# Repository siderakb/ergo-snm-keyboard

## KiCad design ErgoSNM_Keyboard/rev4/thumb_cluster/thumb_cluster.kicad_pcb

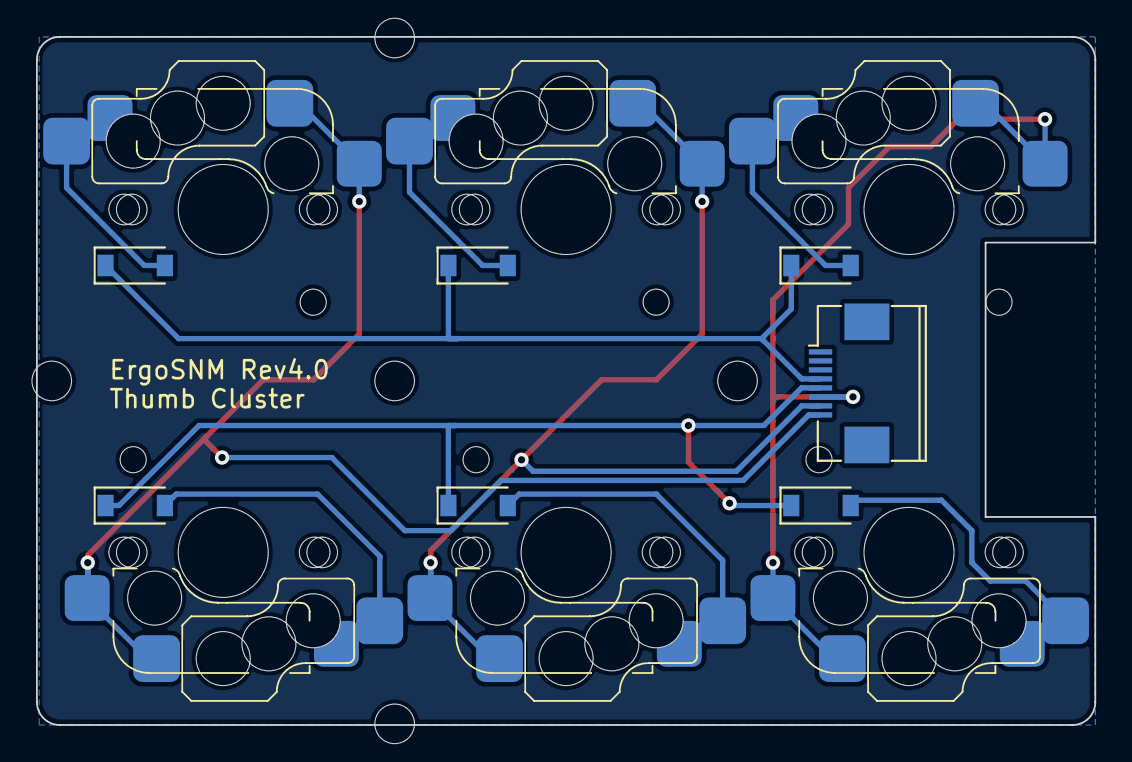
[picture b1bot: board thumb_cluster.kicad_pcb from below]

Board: 2 copper layers, 58.8 x 38.2 mm, 18 parts (11 on the bottom side), 11 nets.

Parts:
D1, D2, D3, D4, D5, D6: 1N4148; D_SOD-123
H1, H2, H3, H4, H5: MountingHole; MountingHole_2.2mm_M2
J2: Conn_FPC; FPC_8P_0.5mm_AFC01-S08FCA-00
KEY1, KEY2, KEY3, KEY4, KEY5, KEY6: SW_Push_45deg; SW_MX_Kailh_Choc_V1V2_HotSwap_Hybrid_alt1

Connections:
COL_5: J2.6, KEY1.1, KEY4.1
COL_6: J2.7, KEY2.1, KEY5.1
COL_7: J2.8, KEY3.1, KEY6.1
unnamed: D1.2 (A), KEY1.2
unnamed: D2.2 (A), KEY2.2
unnamed: D3.2 (A), KEY3.2
unnamed: D4.2 (A), KEY4.2
unnamed: D5.2 (A), KEY5.2
unnamed: D6.2 (A), KEY6.2
ROW_4: D1.1 (K), D2.1 (K), D3.1 (K), J2.4
ROW_5: D4.1 (K), D5.1 (K), D6.1 (K), J2.5

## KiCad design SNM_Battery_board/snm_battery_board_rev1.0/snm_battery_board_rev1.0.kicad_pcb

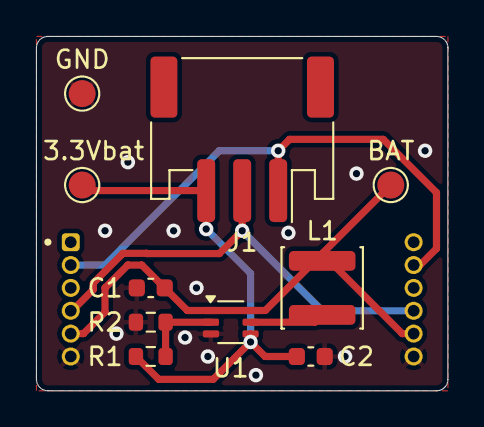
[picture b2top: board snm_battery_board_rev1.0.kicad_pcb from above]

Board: 2 copper layers, 22.9 x 19.7 mm, 11 parts (0 on the bottom side), 7 nets.

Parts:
C1, C2: 10uF; C_0603_1608Metric
J1: Ext. SW_SPDT; JST_PH_S3B-PH-SM4-TB_1x03-1MP_P2.00mm_Horizontal
L1: 4.7uH; L_Changjiang_FNR4030S
M1: SNM_Battery_board
R1: 1.2M; R_0603_1608Metric
R2: 220k; R_0603_1608Metric
TP1: BAT; TestPoint_Pad_D1.5mm
TP2: 3.3Vbat; TestPoint_Pad_D1.5mm
TP3: GND; TestPoint_Pad_D1.5mm
U1: TPS61220DCK; Texas_R-PDSO-G6

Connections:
3.3Vin: J1.1, M1.2, M1.8
3.3Vout: J1.2, M1.4, M1.10
/Vbat: C2.1, J1.3, R1.1, TP2.1, U1.4 (VOUT)
GND: C1.2, C2.2, M1.6, M1.12, R2.2, TP3.1, U1.3 (GND)
unnamed: R1.2, R2.1, U1.2 (FB)
unnamed: L1.2, U1.5 (L)
VBAT: C1.1, L1.1, M1.5, M1.11, TP1.1, U1.1 (VIN), U1.6 (EN)

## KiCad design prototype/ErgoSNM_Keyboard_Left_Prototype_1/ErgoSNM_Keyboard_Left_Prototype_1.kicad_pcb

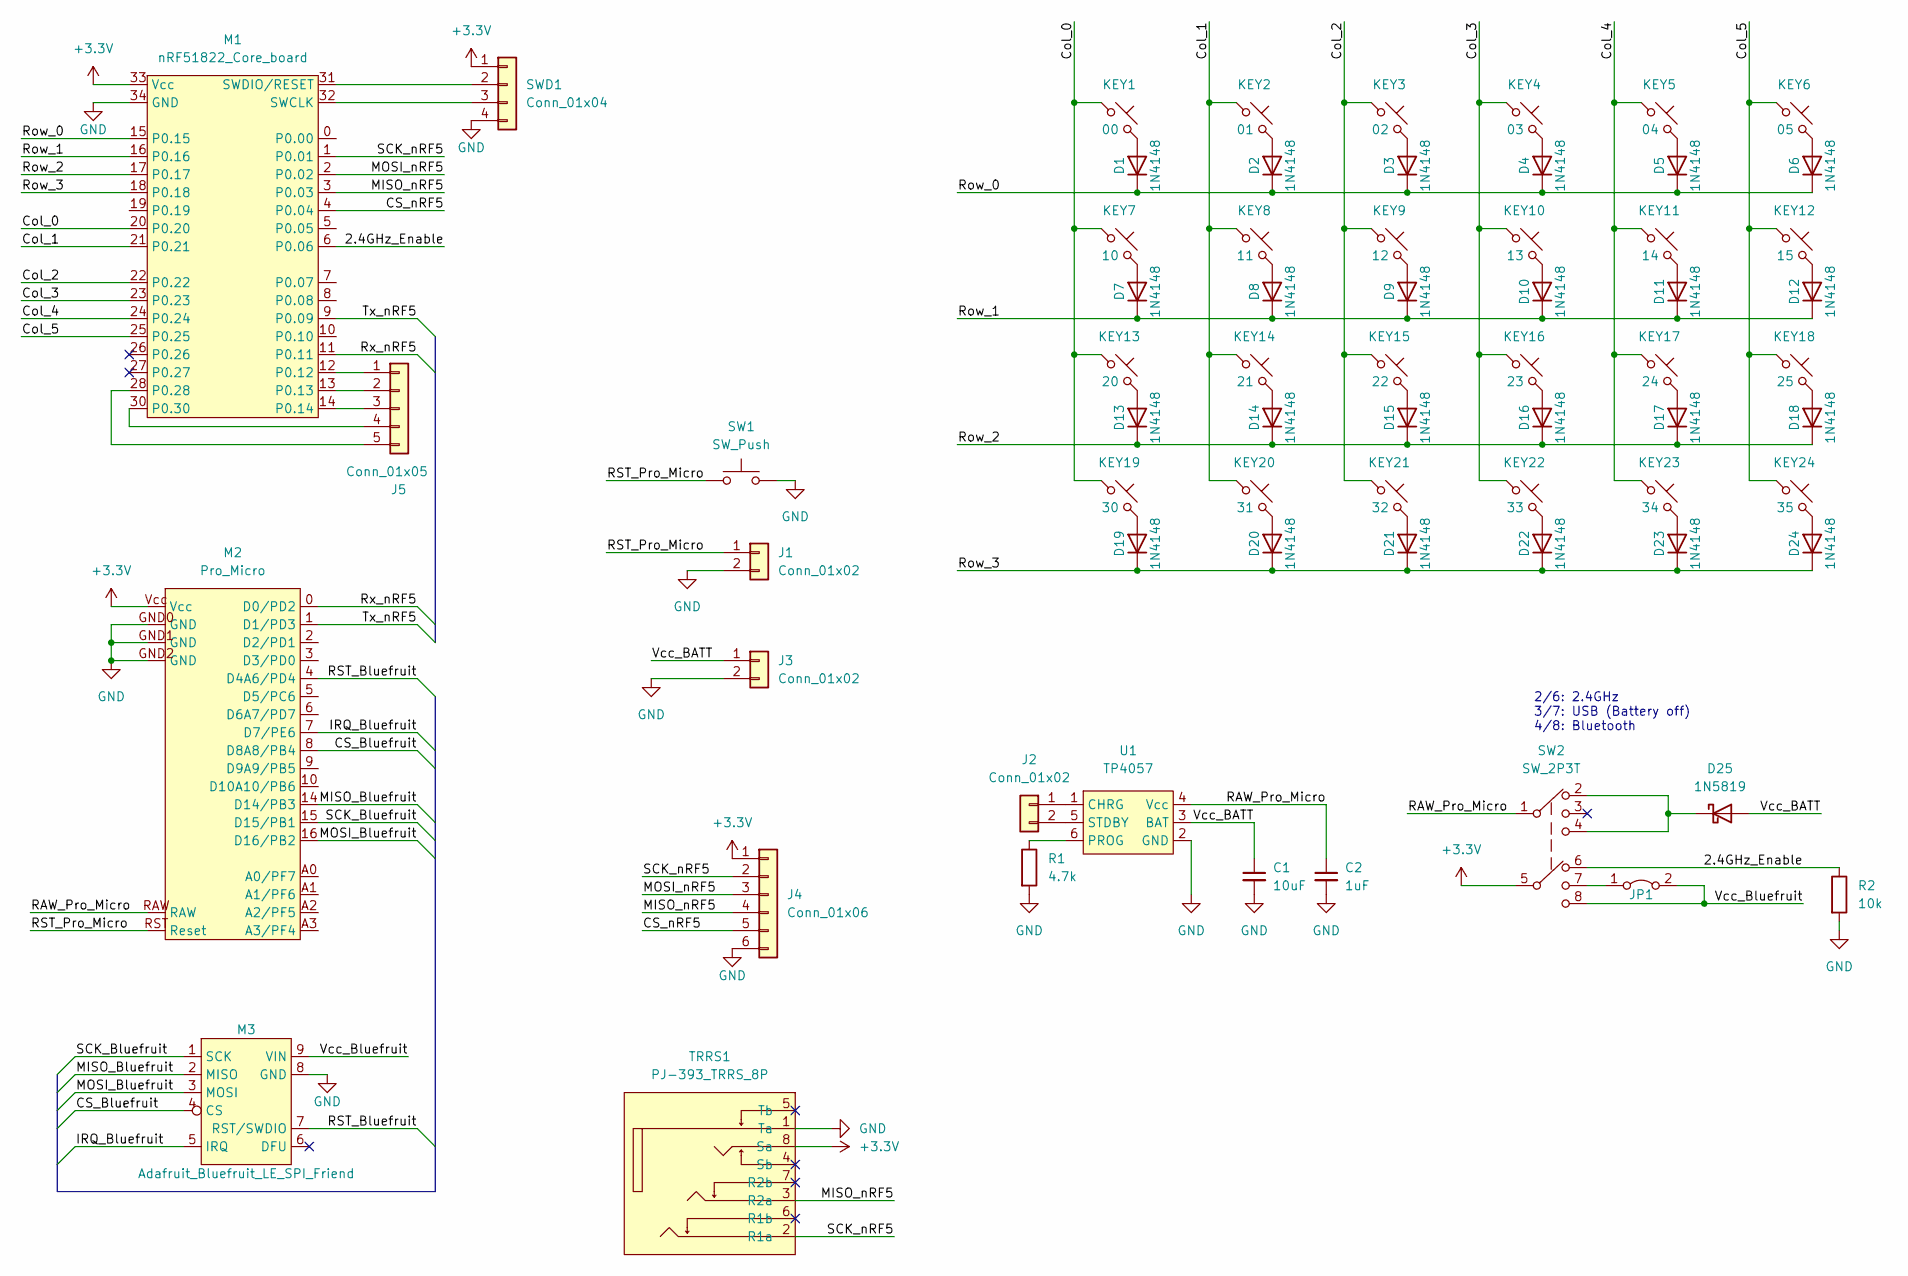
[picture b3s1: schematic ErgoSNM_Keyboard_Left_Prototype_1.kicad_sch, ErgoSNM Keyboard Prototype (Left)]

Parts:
C1: 10uF; C_0201_0603Metric_Pad0.64x0.40mm_HandSolder
C2: 1uF; C_0201_0603Metric_Pad0.64x0.40mm_HandSolder
D1, D2, D3, D4, D5, D6, D7, D8, D9, D10, D11, D12, D13, D14, D15, D16, D17, D18, D19, D20, D21, D22, D23, D24: 1N4148; D_0603_1608Metric_Pad1.05x0.95mm_HandSolder
D25: 1N5819; D_DO-41_SOD81_P10.16mm_Horizontal
J1, J2: Conn_01x02; PinHeader_1x02_P2.54mm_Horizontal
J3: Conn_01x02; JST_EH_B2B-EH-A_1x02_P2.50mm_Vertical
J4: Conn_01x06; PinHeader_1x06_P2.54mm_Vertical
J5: Conn_01x05; PinHeader_1x05_P2.54mm_Vertical
JP1: Jumper_2_Bridged; SolderJumper-2_P1.3mm_Open_TrianglePad1.0x1.5mm
KEY1: 00; MX_Switch_Gateron_socket_A
KEY2: 01; MX_Switch_Gateron_socket_A
KEY3: 02; MX_Switch_Gateron_socket_A
KEY4: 03; MX_Switch_Gateron_socket_A
KEY5: 04; MX_Switch_Gateron_socket_A
KEY6: 05; MX_Switch_Gateron_socket_A
KEY7: 10; MX_Switch_Gateron_socket_A
KEY8: 11; MX_Switch_Gateron_socket_A
KEY9: 12; MX_Switch_Gateron_socket_A
KEY10: 13; MX_Switch_Gateron_socket_A
KEY11: 14; MX_Switch_Gateron_socket_A
KEY12: 15; MX_Switch_Gateron_socket_A
KEY13: 20; MX_Switch_Gateron_socket_A
KEY14: 21; MX_Switch_Gateron_socket_A
KEY15: 22; MX_Switch_Gateron_socket_A
KEY16: 23; MX_Switch_Gateron_socket_A
KEY17: 24; MX_Switch_Gateron_socket_A
KEY18: 25; MX_Switch_Gateron_socket_A
KEY19: 30; MX_Switch_Gateron_socket_A
KEY20: 31; MX_Switch_Gateron_socket_A
KEY21: 32; MX_Switch_Gateron_socket_A
KEY22: 33; MX_Switch_Gateron_socket_A
KEY23: 34; MX_Switch_Gateron_socket_A
KEY24: 35; MX_Switch_Gateron_socket_A
M1: nRF51822_Core_board; Core51822
M2: Pro_Micro
M3: Adafruit_Bluefruit_LE_SPI_Friend; PinHeader_1x09_P2.54mm_Vertical
R1: 4.7k; R_0201_0603Metric_Pad0.64x0.40mm_HandSolder
R2: 10k; R_0201_0603Metric_Pad0.64x0.40mm_HandSolder
SW1: SW_Push; SW_Push_1P1T_NO_CK_KSC6xxJ
SW2: SW_2P3T; MSK-23D20-T
SWD1: Conn_01x04; PinHeader_1x04_P2.54mm_Horizontal
TRRS1: PJ-393_TRRS_8P; PJ-393
U1: TP4057; SOT-23-6_Handsoldering

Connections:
+3V3: J4.1, M1.33 (Vcc), M2.Vcc, SW2.5, SWD1.1, TRRS1.8 (Sa)
/2.4GHz_Enable: M1.6 (P0.06), R2.1, SW2.6
/CS_Bluefruit: M2.8 (D8A8/PB4), M3.4 (CS)
/CS_nRF5: J4.5, M1.4 (P0.04)
/Col_0: KEY1.1, KEY7.1, KEY13.1, KEY19.1, M1.20 (P0.20)
/Col_1: KEY2.1, KEY8.1, KEY14.1, KEY20.1, M1.21 (P0.21)
/Col_2: KEY3.1, KEY9.1, KEY15.1, KEY21.1, M1.22 (P0.22)
/Col_3: KEY4.1, KEY10.1, KEY16.1, KEY22.1, M1.23 (P0.23)
/Col_4: KEY5.1, KEY11.1, KEY17.1, KEY23.1, M1.24 (P0.24)
/Col_5: KEY6.1, KEY12.1, KEY18.1, KEY24.1, M1.25 (P0.25)
/IRQ_Bluefruit: M2.7 (D7/PE6), M3.5 (IRQ)
/MISO_Bluefruit: M2.14 (D14/PB3), M3.2 (MISO)
/MISO_nRF5: J4.4, M1.3 (P0.03), TRRS1.3 (R2a)
/MOSI_Bluefruit: M2.16 (D16/PB2), M3.3 (MOSI)
/MOSI_nRF5: J4.3, M1.2 (P0.02)
/RAW_Pro_Micro: C2.1, M2.RAW, SW2.1, U1.4 (Vcc)
/RST_Bluefruit: M2.4 (D4A6/PD4), M3.7 (RST/SWDIO)
/RST_Pro_Micro: J1.1, M2.RST (Reset), SW1.2
/Row_0: D1.1 (K), D2.1 (K), D3.1 (K), D4.1 (K), D5.1 (K), D6.1 (K), M1.15 (P0.15)
/Row_1: D7.1 (K), D8.1 (K), D9.1 (K), D10.1 (K), D11.1 (K), D12.1 (K), M1.16 (P0.16)
/Row_2: D13.1 (K), D14.1 (K), D15.1 (K), D16.1 (K), D17.1 (K), D18.1 (K), M1.17 (P0.17)
/Row_3: D19.1 (K), D20.1 (K), D21.1 (K), D22.1 (K), D23.1 (K), D24.1 (K), M1.18 (P0.18)
/Rx_nRF5: M1.11 (P0.11), M2.0 (D0/PD2)
/SCK_Bluefruit: M2.15 (D15/PB1), M3.1 (SCK)
/SCK_nRF5: J4.2, M1.1 (P0.01), TRRS1.2 (R1a)
/Tx_nRF5: M1.9 (P0.09), M2.1 (D1/PD3)
/Vcc_BATT: C1.1, D25.2 (A), J3.1, U1.3 (BAT)
/Vcc_Bluefruit: JP1.2 (B), M3.9 (VIN), SW2.8
GND: C1.2, C2.2, J1.2, J3.2, J4.6, M1.34 (GND), M2.GND0 (GND), M2.GND1 (GND), M2.GND2 (GND), M3.8 (GND), R1.2, R2.2, SW1.1, SWD1.4, TRRS1.1 (Ta), U1.2 (GND)
unnamed: D1.2 (A), KEY1.2
unnamed: D2.2 (A), KEY2.2
unnamed: D3.2 (A), KEY3.2
unnamed: D4.2 (A), KEY4.2
unnamed: D5.2 (A), KEY5.2
unnamed: D6.2 (A), KEY6.2
unnamed: D7.2 (A), KEY7.2
unnamed: D8.2 (A), KEY8.2
unnamed: D9.2 (A), KEY9.2
unnamed: D10.2 (A), KEY10.2
unnamed: D11.2 (A), KEY11.2
unnamed: D12.2 (A), KEY12.2
unnamed: D13.2 (A), KEY13.2
unnamed: D14.2 (A), KEY14.2
unnamed: D15.2 (A), KEY15.2
unnamed: D16.2 (A), KEY16.2
unnamed: D17.2 (A), KEY17.2
unnamed: D18.2 (A), KEY18.2
unnamed: D19.2 (A), KEY19.2
unnamed: D20.2 (A), KEY20.2
unnamed: D21.2 (A), KEY21.2
unnamed: D22.2 (A), KEY22.2
unnamed: D23.2 (A), KEY23.2
unnamed: D24.2 (A), KEY24.2
unnamed: D25.1 (K), SW2.2, SW2.4
unnamed: J2.1, U1.1 (CHRG)
unnamed: J2.2, U1.5 (STDBY)
unnamed: JP1.1 (A), SW2.7
unnamed: J5.1, M1.12 (P0.12)
unnamed: J5.2, M1.13 (P0.13)
unnamed: J5.3, M1.14 (P0.14)
unnamed: J5.5, M1.28 (P0.28)
unnamed: J5.4, M1.30 (P0.30)
unnamed: M1.31 (SWDIO/RESET), SWD1.2
unnamed: M1.32 (SWCLK), SWD1.3
unnamed: R1.1, U1.6 (PROG)

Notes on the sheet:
2/6: 2.4GHz 3/7: USB (Battery off) 4/8: Bluetooth

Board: 2 copper layers, 67 parts (0 on the bottom side), 65 nets, no tracks yet.

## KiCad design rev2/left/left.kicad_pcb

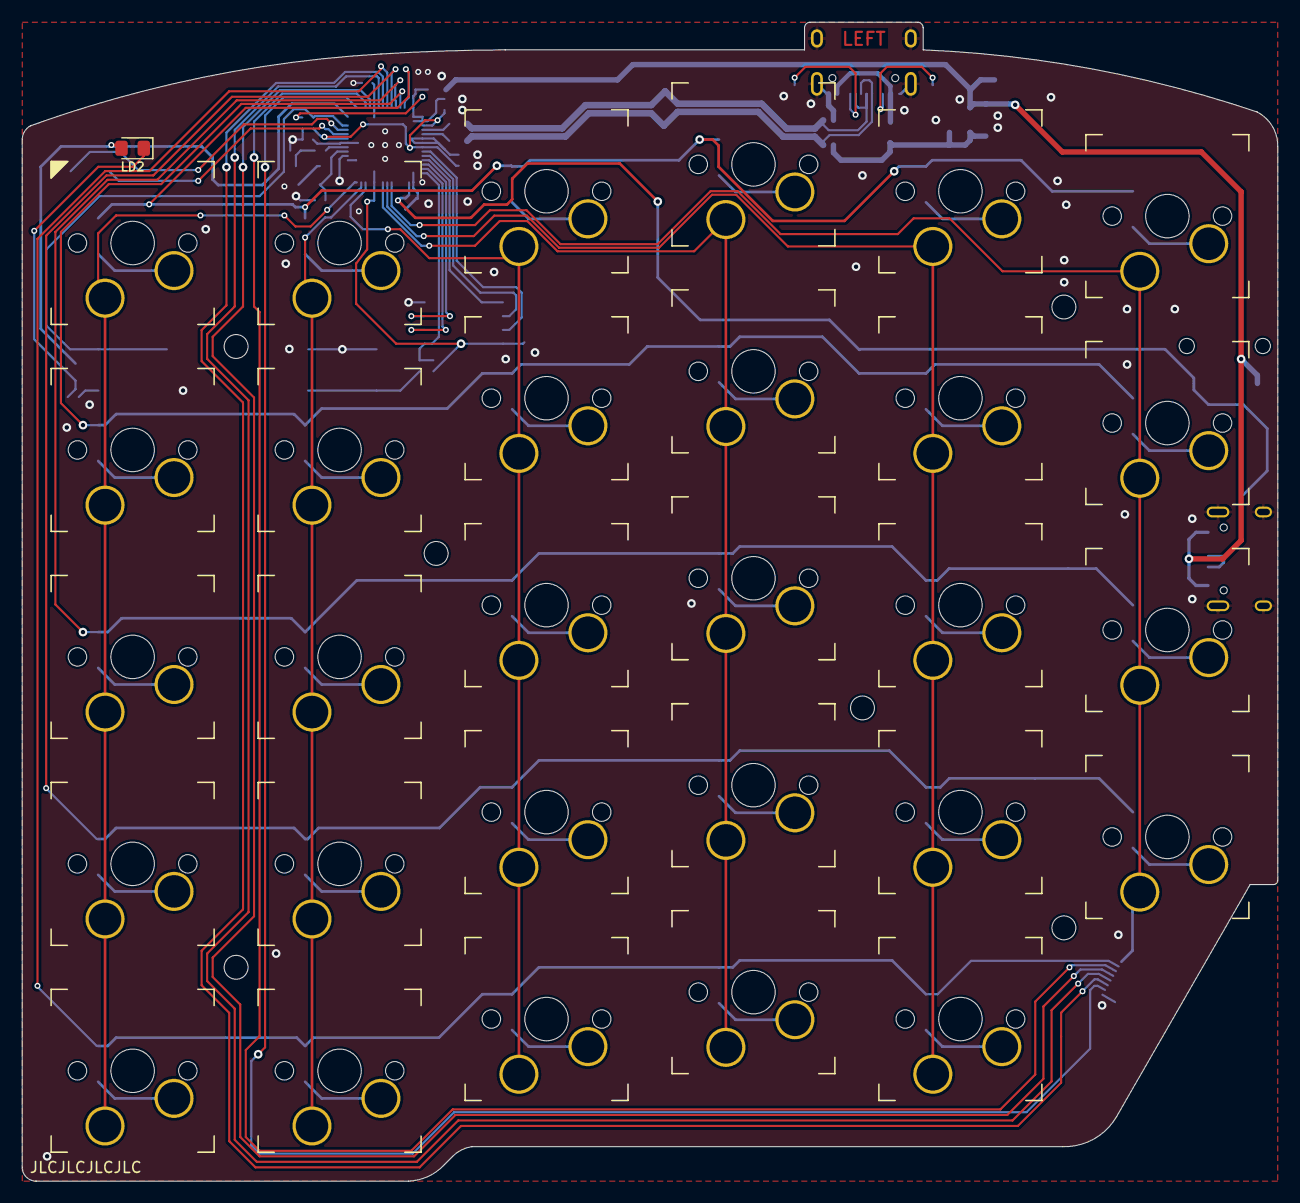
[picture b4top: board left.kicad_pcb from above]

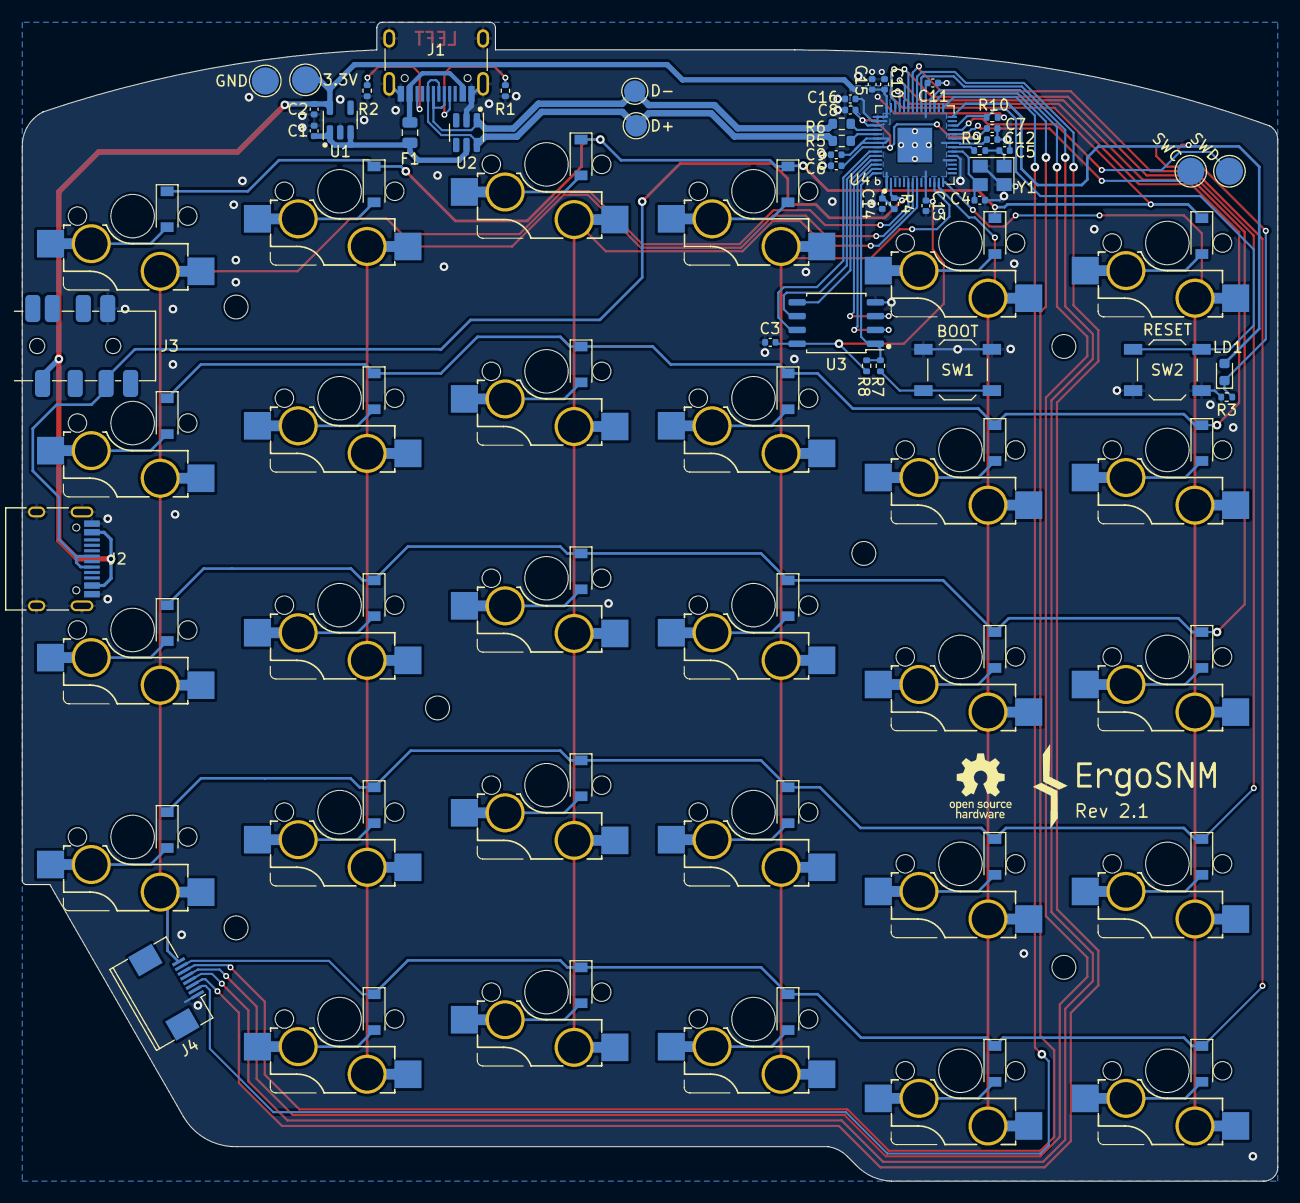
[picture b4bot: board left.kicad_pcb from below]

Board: 2 copper layers, 115.6 x 106.7 mm, 110 parts (80 on the bottom side), 72 nets.

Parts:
C1, C2, C8, C16: 1uF; C_0402_1005Metric
C3, C6, C7, C9, C10, C11, C12, C13, C14, C15: 100nF; C_0402_1005Metric
C4, C5: 20pF; C_0402_1005Metric
D1, D2, D3, D4, D5, D6, D7, D8, D9, D10, D11, D12, D13, D14, D15, D16, D17, D18, D19, D20, D21, D22, D23, D24, D25, D26, D27, D28, D29: 1N4148; D_SOD-123
F1: 500mA, 6V; Fuse_0805_2012Metric
H1, H2, H3, H4, H5, H6: MountingHole; MountingHole_2.2mm_M2
J1, J2: USB_C_Receptacle_USB2.0; USB_C_Receptacle_HRO_TYPE-C-31-M-12
J3: PJ-393_TRRS_8P; PJ-393 8P TRRS
J4: Conn_01x08; FPC_8P_0.5mm_AFC01-S08FCA-00
KEY1, KEY2, KEY3, KEY4, KEY5, KEY6, KEY7, KEY8, KEY9, KEY10, KEY11, KEY12, KEY13, KEY14, KEY15, KEY16, KEY17, KEY18, KEY19, KEY20, KEY21, KEY22, KEY23, KEY24, KEY25, KEY26, KEY27, KEY28, KEY29: SW_Push_45deg; MX_switch_PTH_hotswap_A
LD1: Red; LED_0603_1608Metric
LD2: LED; LED_0805_2012Metric_Pad1.15x1.40mm_HandSolder
R1, R2, R4: 5.1k; R_0402_1005Metric
R3, R7, R9: 1k; R_0402_1005Metric
R5, R6: 27; R_0603_1608Metric
R8, R10: 10k; R_0402_1005Metric
SW1: BOOT; SW_SPST_TL3342
SW2: RESET; SW_SPST_TL3342
TP1, TP4, TP5, TP6: TestPoint; TestPoint_Pad_D2.5mm
TP2, TP3: TestPoint; TestPoint_Pad_D2.0mm
U1: RT9013-33GB; SOT-23-5
U2: SRV05-4; SOT-23-6
U3: W25Q128JVS; SOIC-8_5.23x5.23mm_P1.27mm
U4: RP2040; QFN-56-1EP_7x7mm_P0.4mm_EP3.2x3.2mm
Y1: 12MHz; Crystal_SMD_3225-4Pin_3.2x2.5mm

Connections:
+1V1: C6.1, C7.1, C8.1, U4.23 (DVDD), U4.45 (VREG_VOUT), U4.50 (DVDD)
+3V3: C2.1, C3.1, C9.1, C10.1, C11.1, C12.1, C13.1, C14.1, C15.1, C16.1, J2.A4 (VBUS), J2.A9 (VBUS), J2.B4 (VBUS), J2.B9 (VBUS), J3.S, R4.2, R8.1, R10.1, TP1.1, U1.5 (VOUT), U3.8 (VCC), U4.1 (IOVDD), U4.10 (IOVDD), U4.18 (GPIO15), U4.22 (IOVDD), U4.33 (IOVDD), U4.42 (IOVDD), U4.43 (ADC_AVDD), U4.44 (VREG_IN), U4.48 (USB_VDD), U4.49 (IOVDD)
+5V: C1.1, F1.2, U1.1 (VIN), U1.3 (EN), U2.5 (VP)
/RP2040/BOOT: R7.1, SW1.2
/RP2040/QSPI_D0: U3.5 (DI(IO0)), U4.53 (QSPI_SD0)
/RP2040/QSPI_D1: U3.2 (DO(IO1)), U4.55 (QSPI_SD1)
/RP2040/QSPI_D2: U3.3 (IO2), U4.54 (QSPI_SD2)
/RP2040/QSPI_D3: U3.7 (IO3), U4.51 (QSPI_SD3)
/RP2040/QSPI_SCLK: U3.6 (CLK), U4.52 (QSPI_SCLK)
/RP2040/QSPI_SS: R7.2, R8.2, U3.1 (~CS), U4.56 (QSPI_SS)
/RP2040/SWCLK: TP5.1, U4.24 (SWCLK)
/RP2040/SWDIO: TP6.1, U4.25 (SWD)
/RP2040/~RESET: R10.2, SW2.2, U4.26 (RUN)
/USB_D+: J1.A6 (D+), J1.B6 (D+), R5.1, TP3.1, U2.6 (IO4)
/USB_D-: J1.A7 (D-), J1.B7 (D-), R6.1, TP2.1, U2.1 (IO1)
COL_0: KEY1.1, KEY7.1, KEY13.1, KEY19.1, KEY25.1, U4.14 (GPIO11)
COL_1: KEY2.1, KEY8.1, KEY14.1, KEY20.1, KEY26.1, U4.13 (GPIO10)
COL_2: KEY3.1, KEY9.1, KEY15.1, KEY21.1, KEY27.1, U4.12 (GPIO9)
COL_3: KEY4.1, KEY10.1, KEY16.1, KEY22.1, KEY28.1, U4.8 (GPIO6)
COL_4: KEY5.1, KEY11.1, KEY17.1, KEY23.1, KEY29.1, U4.7 (GPIO5)
COL_5: J4.8, KEY6.1, KEY12.1, KEY18.1, KEY24.1, U4.6 (GPIO4)
COL_6: J4.4, U4.34 (GPIO22)
COL_7: J4.5, U4.32 (GPIO21)
Encoder_A: J4.3, U4.35 (GPIO23)
Encoder_B: J4.2, U4.29 (GPIO18)
GND: C1.2, C2.2, C3.2, C4.1, C5.1, C6.2, C7.2, C8.2, C9.2, C10.2, C11.2, C12.2, C13.2, C14.2, C15.2, C16.2, J1.A1 (GND), J1.A12 (GND), J1.B1 (GND), J1.B12 (GND), J1.S1 (SHIELD), J2.A1 (GND), J2.A12 (GND), J2.B1 (GND), J2.B12 (GND), J2.S1 (SHIELD), J3.T, J4.1, R1.2, R2.2, R3.2, SW1.1, SW2.1, TP4.1, U1.2 (GND), U2.2 (VN), U3.4 (GND), U4.19 (TESTEN), U4.57 (GND), Y1.2, Y1.4
unnamed: C4.2, U4.20 (XIN), Y1.3
unnamed: C5.2, R9.1, Y1.1
unnamed: D1.2 (A), KEY1.2
unnamed: D2.2 (A), KEY2.2
unnamed: D3.2 (A), KEY3.2
unnamed: D4.2 (A), KEY4.2
unnamed: D5.2 (A), KEY5.2
unnamed: D6.2 (A), KEY6.2
unnamed: D7.2 (A), KEY7.2
unnamed: D8.2 (A), KEY8.2
unnamed: D9.2 (A), KEY9.2
unnamed: D10.2 (A), KEY10.2
unnamed: D11.2 (A), KEY11.2
unnamed: D12.2 (A), KEY12.2
unnamed: D13.2 (A), KEY13.2
unnamed: D14.2 (A), KEY14.2
unnamed: D15.2 (A), KEY15.2
unnamed: D16.2 (A), KEY16.2
unnamed: D17.2 (A), KEY17.2
unnamed: D18.2 (A), KEY18.2
unnamed: D19.2 (A), KEY19.2
unnamed: D20.2 (A), KEY20.2
unnamed: D21.2 (A), KEY21.2
unnamed: D22.2 (A), KEY22.2
unnamed: D23.2 (A), KEY23.2
unnamed: D24.2 (A), KEY24.2
unnamed: D25.2 (A), KEY25.2
unnamed: D26.2 (A), KEY26.2
unnamed: D27.2 (A), KEY27.2
unnamed: D28.2 (A), KEY28.2
unnamed: D29.2 (A), KEY29.2
unnamed: J1.A5 (CC1), R1.1
unnamed: J1.B5 (CC2), R2.1
unnamed: LD1.1 (K), LD2.1 (K), R3.1
unnamed: R5.2, U4.47 (USB_DP)
unnamed: R6.2, U4.46 (USB_DM)
unnamed: R9.2, U4.21 (XOUT)
ROW_0: D1.1 (K), D2.1 (K), D3.1 (K), D4.1 (K), D5.1 (K), D6.1 (K), U4.40 (GPIO28_ADC2)
ROW_1: D7.1 (K), D8.1 (K), D9.1 (K), D10.1 (K), D11.1 (K), D12.1 (K), U4.39 (GPIO27_ADC1)
ROW_2: D13.1 (K), D14.1 (K), D15.1 (K), D16.1 (K), D17.1 (K), D18.1 (K), U4.38 (GPIO26_ADC0)
ROW_3: D19.1 (K), D20.1 (K), D21.1 (K), D22.1 (K), D23.1 (K), D24.1 (K), U4.37 (GPIO25)
ROW_4: D25.1 (K), D26.1 (K), D27.1 (K), D28.1 (K), D29.1 (K), J4.7, U4.36 (GPIO24)
ROW_5: J4.6, U4.31 (GPIO20)
SERIAL: J2.A6 (D+), J2.B6 (D+), J3.R1, R4.1, U4.2 (GPIO0)
STATE_LED: LD1.2 (A), LD2.2 (A), U4.28 (GPIO17)
VBUS: F1.1, J1.A4 (VBUS), J1.A9 (VBUS), J1.B4 (VBUS), J1.B9 (VBUS)

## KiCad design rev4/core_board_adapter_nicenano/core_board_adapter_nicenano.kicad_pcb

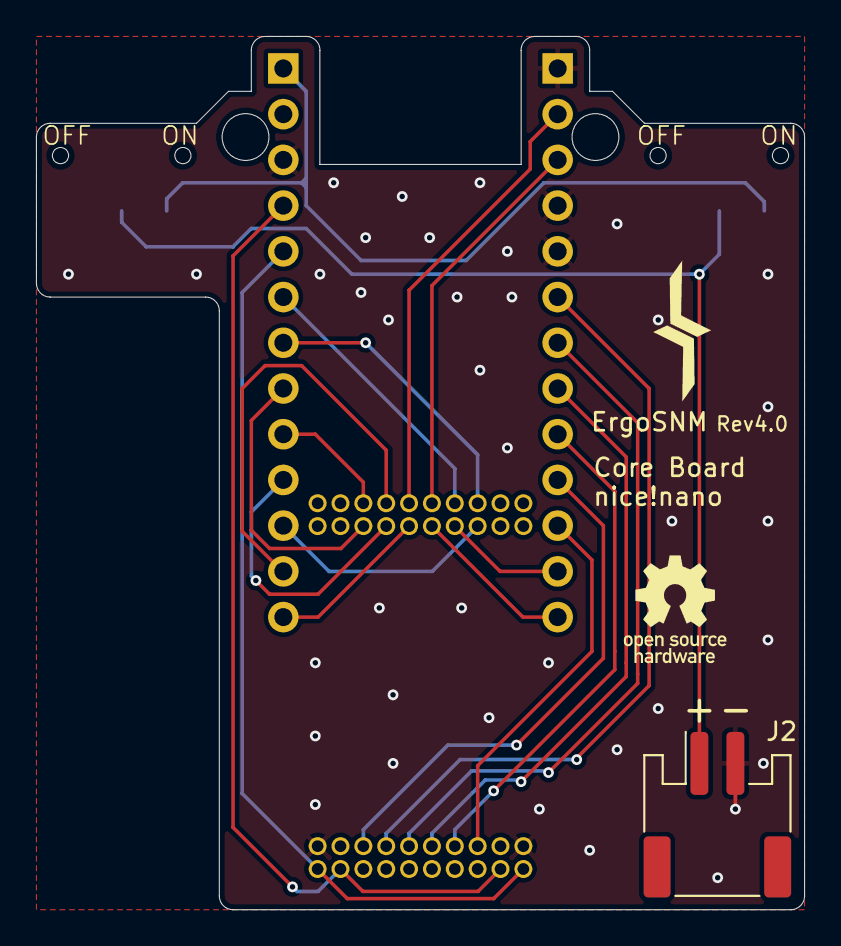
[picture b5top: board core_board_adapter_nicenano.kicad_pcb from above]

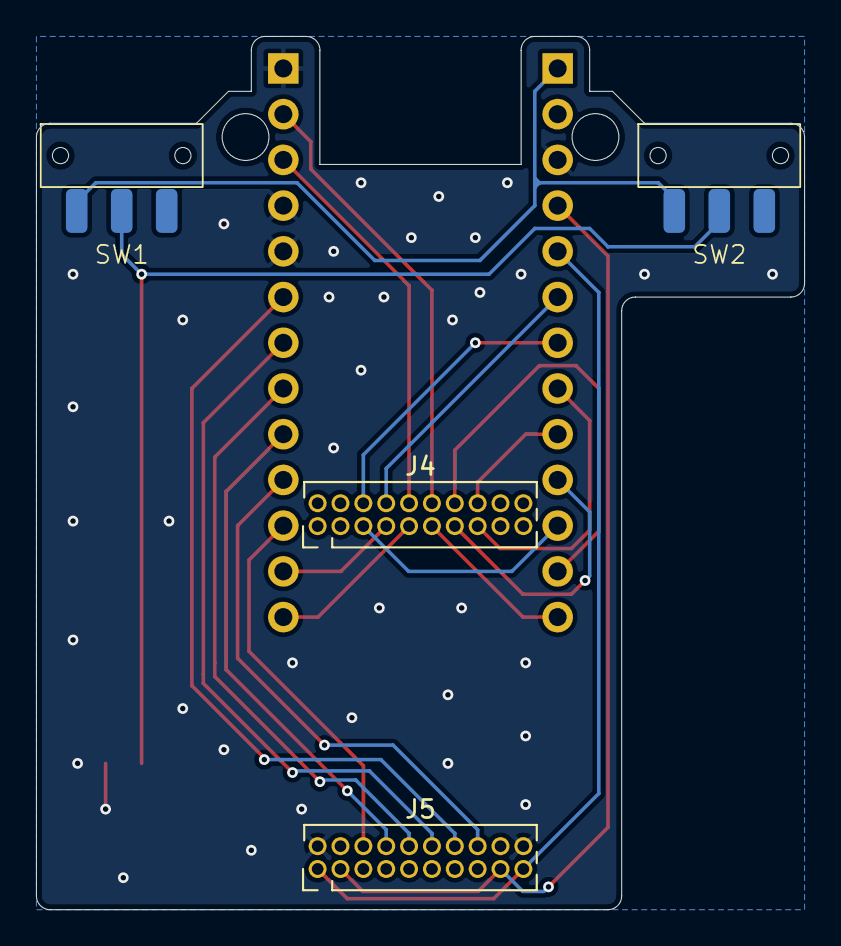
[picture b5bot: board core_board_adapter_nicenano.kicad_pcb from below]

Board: 2 copper layers, 42.7 x 48.5 mm, 9 parts (6 on the bottom side), 23 nets.

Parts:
H1, H2: MountingHole; MountingHole_2.7mm_M2.5_ISO7380
J1, J3: Conn_01x13; PinHeader_1x13_P2.54mm_Vertical
J2: Conn_Batt; JST_PH_S2B-PH-SM4-TB_1x02-1MP_P2.00mm_Horizontal
J4, J5: Conn_02x10_Odd_Even; PinHeader_2x10_P1.27mm_Vertical
SW1, SW2: SW_SPDT; 9_3.5_3.5_switch

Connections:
+3.3V: J3.5, J5.1, J5.19
+BATT: J3.1, SW1.1 (A), SW2.1 (A)
GND: J1.1, J1.4, J1.5, J2.2, J3.3, J5.2, J5.20
unnamed: J2.1, SW1.2 (B), SW2.2 (B)
P0.02: J3.8, J4.15
P0.06: J1.2, J4.12
P0.08: J1.3, J4.10
P0.09: J3.13, J4.11
P0.10: J3.12, J4.14
P0.11: J1.11, J5.6
P0.17: J1.6, J5.14
P0.20: J1.7, J5.12
P0.22: J1.8, J5.10
P0.24: J1.9, J5.8
P0.29: J3.7, J4.6
P0.31: J3.6, J4.8
P1.00: J1.10, J5.16
P1.04: J1.12, J4.7
P1.06: J1.13, J4.9
P1.11: J3.11, J4.5
P1.13: J3.10, J4.13
P1.15: J3.9, J4.16
RESET: J3.4, J5.3, J5.17

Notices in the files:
ErgoSNM_Keyboard/rev4/thumb_cluster/thumb_cluster.kicad_pcb:
Open source hardware, CERN-OHL-P v2
